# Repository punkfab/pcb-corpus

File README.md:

# pcb-corpus

235 real KiCad boards from 170 open-source hardware repositories, prepared as a benchmark for
PCB placement and routing tools. Each board comes as its designer shipped it and as an unrouted copy, with
its own project rules.

It exists because the public routing benchmarks are built on KiCad 5 files with no project file, so every
board is judged against KiCad's default rules. These are current designs judged against their own.

## What is in a board folder

| file | what it is |
|---|---|
| `board.kicad_pcb` | the designer's board, unmodified |
| `board.kicad_pro` | its project file: net classes, clearances, DRC severities |
| `board.kicad_dru` | its custom rules, when the project has them |
| `unrouted.kicad_pcb` | the same board with tracks, vias and zone fills removed; placement kept |
| `LICENSE` (or as named upstream) | the source repository's licence file at the pinned commit |
| `SOURCE.json` | repository, commit, path, licence, and what was changed |

`manifest.json` lists every board with its statistics. `splits.json` is the original three-way split by size:
easy (under 40 connections, 37 boards), medium (40 to 149, 112) and hard (150 and up, 86).

## What qualified

A board is here if:

- its repository carries an open-hardware or permissive licence that GitHub recognises,
- a `.kicad_pro` sits beside the `.kicad_pcb`,
- it opens in KiCad 9, has 1 to 4 copper layers and at least 5 parts on nets,
- and its designer's routing leaves no connection open.

158 of the 235 boards have error-level DRC violations under their own rules as designed. `ref_drv` in
the manifest is that count. For a "clean pass" comparison (fully connected, zero DRC errors), use the
77 boards where it is 0.

Mix: 178 two-layer, 57 four-layer.
Licences: MIT 75, GPL-3.0 67, CERN-OHL-S-2.0 25, CERN-OHL-P-2.0 25, Apache-2.0 19, CC-BY-SA-4.0 10, CERN-OHL-W-2.0 5, CC-BY-4.0 4, BSD-3-Clause 3, CC0-1.0 2.

## Groups and difficulty

`features.json` describes every board: size and density, stackup, packages, project rules, how its designer
routed it, wiring estimates, and what is on it. `groups.json` sorts the boards into overlapping groups, and
[GROUPS.md](GROUPS.md) has the full table with a baseline score for each group.

| kind | groups |
|---|---|
| size | `small` 37, `medium` 112, `large` 66, `xlarge` 20 |
| stackup | `two-layer` 178, `four-layer` 57, `inner-planes` 57, `no-pour` 13 |
| technology | `through-hole` 43, `surface-mount` 72, `double-sided` 99, `fine-pitch` 113, `bga` 7, `dense` 60, `sparse` 59 |
| constraints | `diff-pairs` 80, `shaped-outline` 85, `cutouts` 55, `keepouts` 63, `net-classes` 114, `custom-rules` 22, `tight-rules` 56 |
| wiring | `tangled` 59, `untangled` 55, `via-heavy` 63, `single-sided-routing` 23 |
| on the board | `usb`, `usb-c`, `ethernet`, `can-rs485`, `wireless`, `crystal`, `switching-regulator`, `battery`, `display`, `audio`, `motor-power`, `memory`, `sensor`, `fpga`, `keyboard`, `addressable-leds` |
| controller | `esp32`, `rp2040`, `stm32`, `avr`, `nrf`, `teensy-module` |
| reference | `clean-reference` 77: zero DRC errors as designed |

The "on the board" and controller groups are detected from net, footprint and value names. They are
useful for slicing results, not ground truth; expect some mislabels.

**Difficulty is measured.** Each board's designer placement is routed by a baseline router and judged by
KiCad DRC. The first baseline is [TraceMaker](https://github.com/DingoOz/TraceMaker) with a 30-second budget
(`baselines/tracemaker-30s.json`):

| tier | meaning | boards | median connections |
|---|---|---|---|
| `difficulty-solved` | routed clean: fully connected, zero error-level DRC | 48 | 58 |
| `difficulty-connects` | 98% or more connected, but not clean | 101 | 88 |
| `difficulty-open` | under 98% connected | 86 | 207 |

Over all 235 boards that baseline routes 20% clean and connects 94.5% of connections. On the 77
`clean-reference` boards it routes 49% clean. What separates easy from hard, by share routed clean:

- **Easiest:** `untangled` 45%, `single-sided-routing` 43%, `small` 43%, `no-pour` 38%, `through-hole` 35%.
- **Hardest:** `xlarge`, `fpga` and `bga` 0%, `tangled` 3%, `crystal` 6%, `large` 8%, `double-sided` 9%, `fine-pitch` 10%, `four-layer` 11%.

The tiers will move as baselines are added: a board is `solved` once any baseline routes it clean.
Add one with `python3 tools/baseline.py --name <name> --cmd '<router> {in} -o {out}'`, then
`python3 tools/groups.py`.

## Using it

- **Routing:** route `unrouted.kicad_pcb`, refill the zones, and run
  `kicad-cli pcb drc --severity-error` on the result with `board.kicad_pro` copied beside it.
- **Placement:** move the parts of `unrouted.kicad_pcb`, then route and judge the same way. The designer's
  placement is the reference.
- A router that reads the board file directly will treat a stale zone fill as copper in its way. The
  unrouted boards have their fills cleared for that reason; refill after routing, before DRC.

The collector that built this, and harnesses that run it, are in
[punkfab/circuit-skills](https://github.com/punkfab/circuit-skills) under `evals/corpus`.

## Licences

This repository is a collection. **Each board keeps the licence of its source repository**, copied into
its folder; see [ATTRIBUTION.md](ATTRIBUTION.md) for the full list. Several are share-alike (GPL-3.0,
CERN-OHL-S, CC-BY-SA): if you redistribute or modify those boards, their terms apply to you.
`unrouted.kicad_pcb` is a modified copy (routing removed) under the same licence as its board.

The licence recorded for a board is the one GitHub detects for its repository. If you are an author
and a board here is under different terms than recorded, or you want it removed, open an issue and it
will be taken down.

The manifest, splits, README and attribution files are released under CC0-1.0.

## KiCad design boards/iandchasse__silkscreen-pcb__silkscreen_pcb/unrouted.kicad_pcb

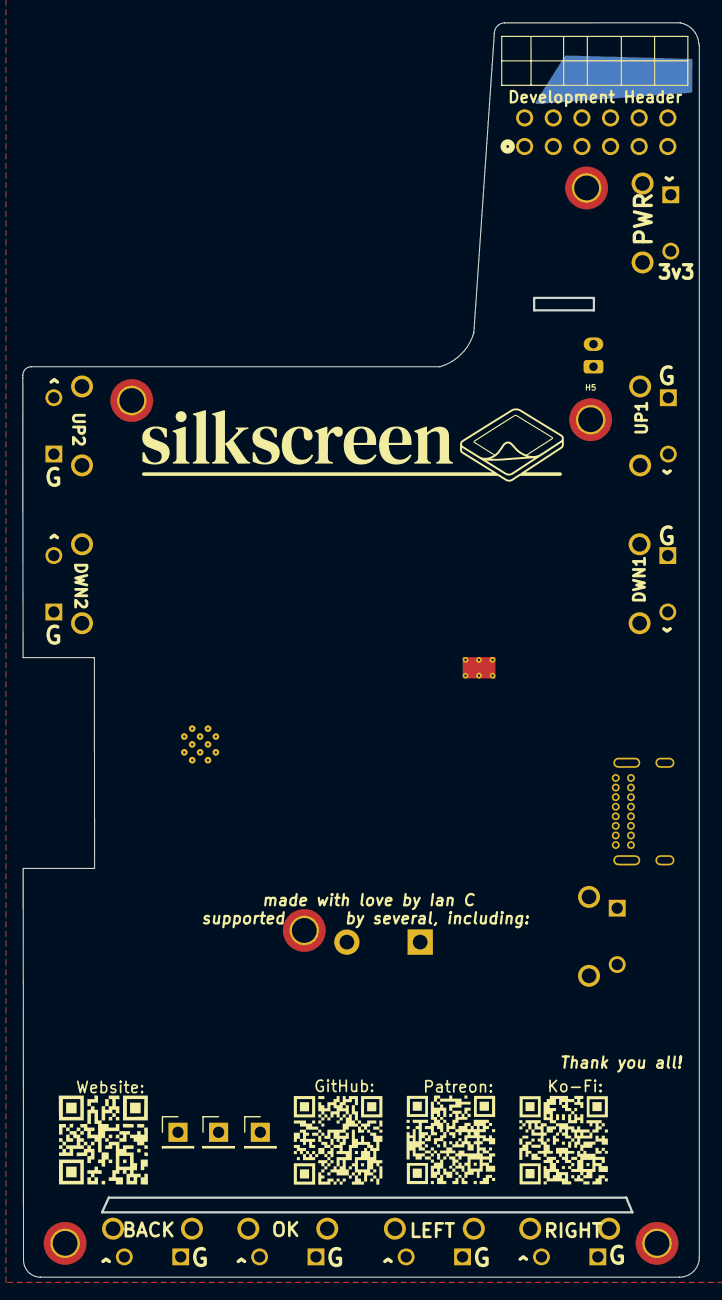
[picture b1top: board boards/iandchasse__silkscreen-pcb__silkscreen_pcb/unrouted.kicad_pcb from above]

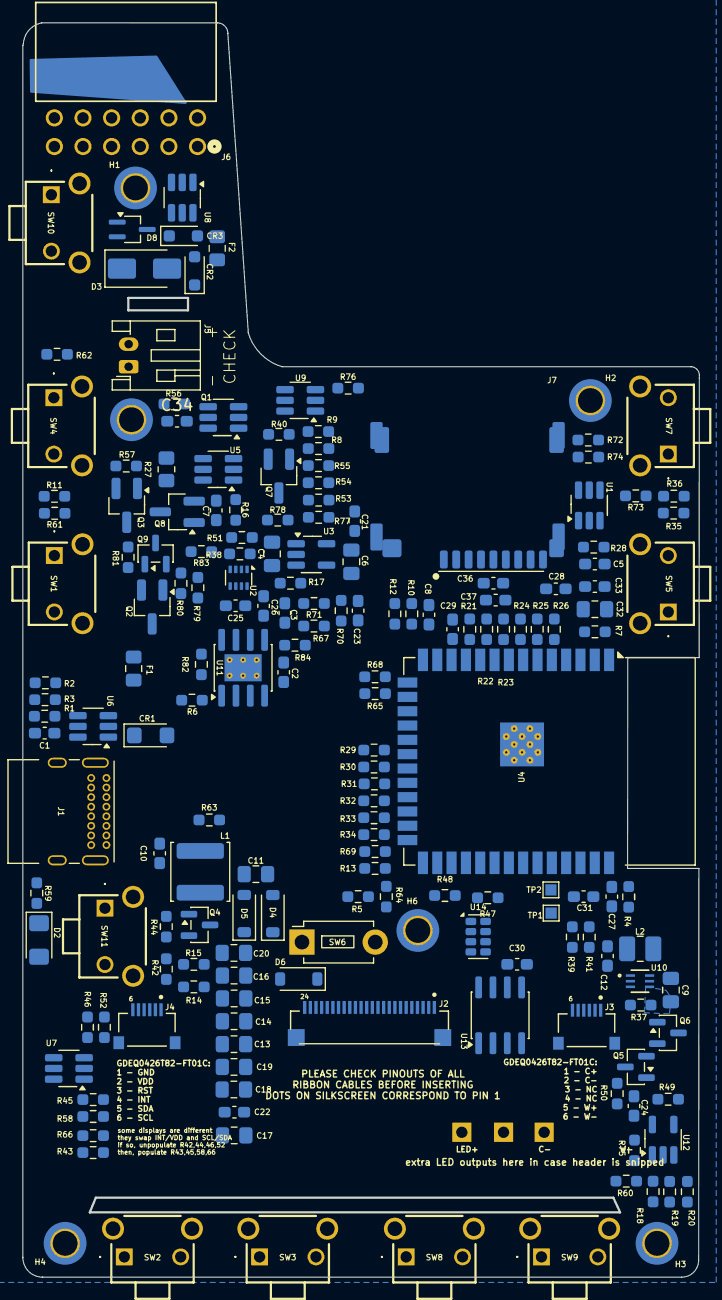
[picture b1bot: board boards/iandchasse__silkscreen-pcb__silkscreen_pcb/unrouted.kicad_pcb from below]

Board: 2 copper layers, 60.0 x 111.3 mm, 185 parts (181 on the bottom side), 114 nets, no tracks yet.

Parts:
C1: 1n; C_0603_1608Metric_Pad1.08x0.95mm_HandSolder
C2: 10u/25V; C_0603_1608Metric_Pad1.08x0.95mm_HandSolder
C3: 10u; C_0603_1608Metric_Pad1.08x0.95mm_HandSolder
C4, C6, C32: 22u; C_0805_2012Metric_Pad1.18x1.45mm_HandSolder
C5, C8, C21, C22, C25, C26, C37: 1u; C_0603_1608Metric_Pad1.08x0.95mm_HandSolder
C7, C23, C24, C30, C31, C33, C36: 0.1u; C_0603_1608Metric_Pad1.08x0.95mm_HandSolder
C9, C11, C13, C14, C15, C16, C17: 4.7u/50V; C_0805_2012Metric_Pad1.18x1.45mm_HandSolder
C10, C12: 4.7u; C_0603_1608Metric_Pad1.08x0.95mm_HandSolder
C18, C19, C20: 1u/50V; C_0805_2012Metric_Pad1.18x1.45mm_HandSolder
C27, C28, C29, C34: 2.2n; C_0603_1608Metric_Pad1.08x0.95mm_HandSolder
CR1: SMF6.5CA; D_SMF
CR2, CR3: TSD05CDYFR; D_SOD-323_HandSoldering
D2: LED; LED_1206_3216Metric_Pad1.42x1.75mm_HandSolder
D3: SMAJ26A; D_SMA
D4, D5, D6: B5819W; D_SOD-123
D8: PESD2IVN-UX; SOT-323_SC-70_Handsoldering
F1: 0805L100WR; Fuse_0805_2012Metric_Pad1.15x1.40mm_HandSolder
F2: 0805L075WR; Fuse_0805_2012Metric_Pad1.15x1.40mm_HandSolder
H1, H2, H3, H4, H5, H6: MountingHole_Pad; MountingHole_2.2mm_M2_DIN965_Pad_TopBottom
J1: USB_C_Receptacle; USB_C_Receptacle_GCT_USB4085
J2: FH34SRJ-24S-0.5SH_50_; HRS_FH34SRJ-24S-0.5SH_50_
J3, J4: FH34SRJ-6S-0.5SH_50_; HRS_FH34SRJ-6S-0.5SH_50_
J5: Conn_01x02; JST_PH_S2B-PH-K_1x02_P2.00mm_Horizontal
J6: PPPC062LJBN-RC; CONN_PPPC062LJBN-RC_SUL
J7: Micro_SD_Card; microSD_PushPush_TFPUSH-MEM2075
L1: 47uH; L_APV_ANR5040
L2: 10u; L_1008_2520Metric_Pad1.43x2.20mm_HandSolder
Q1: FS8205A; SOT-23-6_Handsoldering
Q2, Q3, Q7, Q8: AO3401A; SOT-23_Handsoldering
Q4: IRLML6346TRPBF; SOT-23
Q5, Q6, Q9: BSS138; SOT-23
R1, R10, R12, R15, R39, R49, R50, R70, R80, R81, R82: 1M; R_0603_1608Metric_Pad0.98x0.95mm_HandSolder
R2, R3: 5.1k; R_0603_1608Metric_Pad0.98x0.95mm_HandSolder
R4, R5, R7, R8, R9, R13, R28, R53, R54, R55, R56, R62, R72: 10k; R_0603_1608Metric_Pad0.98x0.95mm_HandSolder
R6: 4.7k; R_0603_1608Metric_Pad0.98x0.95mm_HandSolder
R11: 12k; R_0603_1608Metric_Pad0.98x0.95mm_HandSolder
R14: 2.2; R_0603_1608Metric_Pad0.98x0.95mm_HandSolder
R16, R78: 1k; R_0603_1608Metric_Pad0.98x0.95mm_HandSolder
R17: 2M; R_0603_1608Metric_Pad0.98x0.95mm_HandSolder
R18: 5.6k; R_0603_1608Metric_Pad0.98x0.95mm_HandSolder
R19: 20k; R_0603_1608Metric_Pad0.98x0.95mm_HandSolder
R20: 56k; R_0603_1608Metric_Pad0.98x0.95mm_HandSolder
R21, R22, R23, R24, R25, R26, R29, R30, R31, R32, R33, R34, R65, R68, R69: 33; R_0603_1608Metric_Pad0.98x0.95mm_HandSolder
R27: 0; R_0805_2012Metric_Pad1.20x1.40mm_HandSolder
R35: 33k; R_0603_1608Metric_Pad0.98x0.95mm_HandSolder
R36: 68k; R_0603_1608Metric_Pad0.98x0.95mm_HandSolder
R37: 15; R_0603_1608Metric_Pad0.98x0.95mm_HandSolder
R38: 300k; R_0603_1608Metric_Pad0.98x0.95mm_HandSolder
R40, R51, R75, R76, R77, R79: 100k; R_0603_1608Metric_Pad0.98x0.95mm_HandSolder
R41: 120k; R_0603_1608Metric_Pad0.98x0.95mm_HandSolder
R42, R43, R44, R45, R46, R52, R58, R66, R73, R74: 0; R_0603_1608Metric_Pad0.98x0.95mm_HandSolder
R47, R48: 2.2k; R_0603_1608Metric_Pad0.98x0.95mm_HandSolder
R57: 10M; R_0603_1608Metric_Pad0.98x0.95mm_HandSolder
R59: 2k; R_0603_1608Metric_Pad0.98x0.95mm_HandSolder
R60, R61, R63, R64, R83: 100; R_0603_1608Metric_Pad0.98x0.95mm_HandSolder
R67: 510k; R_0603_1608Metric_Pad0.98x0.95mm_HandSolder
R71: 200k; R_0603_1608Metric_Pad0.98x0.95mm_HandSolder
R84: 1; R_0603_1608Metric_Pad0.98x0.95mm_HandSolder
SW1, SW2, SW3, SW4, SW5, SW7, SW8, SW9, SW10, SW11: SW_Push; MJTP1117
SW6: SW_Push; SW_PUSH_1P1T_6x3.5mm_H4.3_APEM_MJTP1243
TP1, TP2: TestPoint; TestPoint_Pad_1.0x1.0mm
TP3, TP4, TP5: TestPoint; PinHeader_1x01_P2.54mm_Vertical
U1, U6, U7, U8, U9: TPD4E1U06DBVR; SOT-23-6_Handsoldering
U2: TPS2116DRL; SOT-583-8
U3: TLV75533PDBV; SOT-23-5_HandSoldering
U4: ESP32-S3-WROOM-1
U5: DW01A; SOT-23-6_Handsoldering
U10: TPS923610DRLR; U_DRL0006A_6L_TEX-M
U11: TP4056-42-ESOP8; SOIC-8-1EP_3.9x4.9mm_P1.27mm_EP2.41x3.3mm_ThermalVias
U12: 74LVC1G04; SOT-23-5_HandSoldering
U13: DS3231MZ; SOIC-8_3.9x4.9mm_P1.27mm
U14: RV-8263-C7; MicroCrystal_C7_SON-8_1.5x3.2mm_P0.9mm

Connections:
3V3: C6.1, C10.2, C21.1, C22.2, C24.1, C30.1, C32.1, C33.1, CR2.1 (I/O), J2.15, J2.16, J6.7, L1.2, Q2.2 (S), Q7.2 (S), R4.2, R5.2, R7.1, R13.1, R28.2, R40.2, R42.1, R47.1, R48.1, R66.1, R70.2, R74.1, R81.2, SW10.2, U3.5 (OUT), U4.2 (3V3), U12.5 (VCC), U13.6 (VBAT), U14.5 (VDD)
/COLOR_SEL_INV: Q6.1 (G), U12.4
/DET_NODE: Q2.1 (G), Q9.3 (D), R81.1
/GDR: J2.2, Q4.1 (G), R15.2
/P+_FUSE: CR3.1 (I/O), F2.1, J6.12
/PIN_2: J4.2, R42.2, R43.2
/PIN_4: J4.4, R44.2, R66.2, U7.1
/PIN_5: J4.5, R45.2, R46.2, U7.4
/PIN_6: J4.6, R52.2, R58.2, U7.6
/PR1: R38.2, R51.1, U2.4 (PR1)
/RESE: J2.3, Q4.2 (S), R14.2
B+: J5.2, Q3.2 (S), R57.2, R79.1
B-: C7.2, C34.2, J5.1, Q1.1, Q9.2 (S), R56.2, R80.1, U5.6 (GND)
BAT_MONIT: C8.1, R10.1, R12.2, U4.12 (IO8)
BUTTON_ADC_1: C27.2, R4.1, R18.2, R19.2, R20.2, R60.2, U4.39 (IO1)
BUTTON_ADC_2: C28.2, R11.2, R28.1, R35.2, R36.2, R61.2, U4.4 (IO4)
C-: D8.1 (A1), J3.2, J6.11, Q6.3 (D), R49.1, TP4.1
CC1: J1.A5 (CC1), R3.1, U6.4
CC2: J1.B5 (CC2), R2.1, U6.3
CE: Q2.3 (D), R82.2, U11.8 (CE)
CHRG: R67.1, U11.7 (~CHRG)
COLOR_SEL: Q5.1 (G), R75.1, U4.33 (IO40), U12.2
DN: J1.A7 (D-), J1.B7 (D-), U4.13 (USB_D-), U6.1
DP: J1.A6 (D+), J1.B6 (D+), U4.14 (USB_D+), U6.6
EINK_SW: C11.2, D5.2 (A), L1.1, Q4.3 (D)
EPD_BUSY: J2.9, R34.1
EPD_CS: J2.12, R31.1
EPD_DC: J2.11, R32.1
EPD_RST: J2.10, R5.1, R33.1
ESP32_EN: C5.1, R7.2, R63.2, U4.3 (EN)
ESP32_IO0: R13.2, R64.2, U4.27 (IO0)
GND: C1.1, C3.2, C4.2, C5.2, C6.2, C8.2, C9.1, C10.1, C12.1, C13.1, C14.1, C15.1, C16.1, C17.1, C18.1, C19.1, C20.1, C21.2, C22.1, C23.2, C24.2, C25.1, C26.2, C27.1, C28.1, C29.2, C30.2, C31.2, C32.2, C33.2, C36.1, C37.1, CR1.2 (GND), CR2.2 (GND), CR3.2 (GND), D3.2 (A2), D6.1 (K), D8.3 (common), H1.1, H2.1, H3.1, H4.1, H5.1, H6.1, J1.A1 (GND), J1.A12 (GND), J1.B1 (GND), J1.B12 (GND), J2.8, J2.17, J2.S1 (SHIELD), J2.S2 (SHIELD__1), J3.S1 (SHIELD), J3.S2 (SHIELD), J4.1, J4.S1 (SHIELD), J4.S2 (SHIELD), J6.1, J6.4, J7.6 (VSS), J7.9 (SHIELD), Q1.3, Q8.1 (G), R1.1, R2.2, R3.2, R6.2, R10.2, R14.1, R15.1, R16.1, R37.2, R41.2, R49.2, R50.2, R51.2, R59.2, R73.1, R75.2, R76.2, R77.2, R82.1, R84.2, SW1.1, SW2.1, SW3.1, SW4.1, SW5.1, SW6.1, SW8.1, SW9.1, SW11.1, U1.2, U2.1 (GND), U3.2 (GND), U4.1 (GND), U4.40 (GND), U4.41 (GND), U6.2, U7.2, U8.2, U9.2, U10.4 (GND), U11.1 (TEMP), U11.3 (GND), U11.9 (EPAD), U12.3 (GND), U13.2 (VCC), U13.5 (GND), U14.2 (VSS), U14.3 (CLKOE)
I2C_SCL: J6.10, R45.1, R47.2, R52.1, U4.32 (IO39), U8.3, U13.8 (SCL), U14.7 (SCL)
I2C_SDA: J6.8, R46.1, R48.2, R58.1, U4.31 (IO38), U8.4, U13.7 (SDA), U14.8 (SDA)
LDO_IN: C4.1, C12.2, L2.1, U2.2 (VOUT), U2.7 (VOUT), U3.1 (IN), U3.3 (EN), U10.1 (VIN)
LED_MONIT: C31.1, R39.2, R41.1, U4.38 (IO2)
LED_SW: C9.2, D3.1 (A1), J3.1, J3.5, J6.5, R39.1, TP3.1, U10.5 (VOUT)
unnamed: C2.2, R84.1
unnamed: C13.2, J2.20
unnamed: C15.2, J2.22
unnamed: C17.2, J2.5
unnamed: C18.2, J2.18
unnamed: C19.2, J2.19
unnamed: C20.2, J2.24
unnamed: D2.1 (K), R59.1
unnamed: C11.1, D4.1 (K), D6.2 (A)
unnamed: C1.2, J1.S1 (SHIELD), R1.2
unnamed: Q3.3 (D), R27.2
unnamed: Q3.1 (G), R56.1, R57.1
unnamed: Q5.2 (S), Q6.2 (S), R37.1, U10.3 (FB)
unnamed: Q7.1 (G), R40.1, R78.2
unnamed: Q8.3 (D), R27.1
unnamed: Q9.1 (G), R79.2, R80.2
unnamed: R11.1, SW4.2
unnamed: R18.1, SW3.2
unnamed: R19.1, SW8.2
unnamed: R20.1, SW9.2
unnamed: R35.1, SW5.2
unnamed: R36.1, R72.2, SW7.2
unnamed: R60.1, SW2.2
unnamed: R61.1, SW1.2
unnamed: R62.1, SW10.1
unnamed: R63.1, SW11.2
unnamed: R64.1, SW6.2
unnamed: R73.2, R74.2, SW7.1
unnamed: R68.2, U4.15 (IO3)
unnamed: R26.1, U4.5 (IO5)
unnamed: R25.1, U4.6 (IO6)
unnamed: R24.1, U4.7 (IO7)
unnamed: R29.2, U4.20 (IO12)
unnamed: R30.2, U4.21 (IO13)
unnamed: R31.2, U4.22 (IO14)
unnamed: R23.1, U4.8 (IO15)
unnamed: R22.1, U4.9 (IO16)
unnamed: R21.1, U4.10 (IO17)
unnamed: R32.2, U4.23 (IO21)
unnamed: R69.1, U4.26 (IO45)
unnamed: R65.1, U4.16 (IO46)
unnamed: R33.2, U4.24 (IO47)
unnamed: R34.2, U4.25 (IO48)
unnamed: C34.1, R16.2, U5.2 (CS)
unnamed: Q1.4, U5.3 (OC)
unnamed: Q1.6, U5.1 (OD)
unnamed: C7.1, R83.1, U5.5 (VCC)
unnamed: R6.1, U11.2 (PROG)
P+: C3.1, C26.1, F2.2, Q8.2 (S), R12.1, R83.2, U2.6 (VIN2), U11.5 (BAT)
PREVGH: C14.2, D5.1 (K), J2.21
PREVGL: C16.2, D4.2 (A), J2.23
PWM_LED: U4.35 (IO42), U10.2 (ADIM)
PWR_BUTTON: C29.1, R62.2, R72.1, R76.1, U4.11 (IO18)
RX: TP1.1, U4.36 (RXD0)
SD_ACTIVATE: R78.1, U4.18 (IO10)
SD_CLK: J7.5 (CLK), R24.2, U1.4
SD_CMD: J7.3 (CMD), R23.2, R55.1, U1.6
SD_DAT0: J7.7 (DAT0), R8.1, R25.2, U9.3
SD_DAT1: J7.8 (DAT1), R9.1, R26.2, U9.1
SD_DAT2: J7.1 (DAT2), R21.2, R53.1, U1.3
SD_DAT3: J7.2 (DAT3/CD), R22.2, R54.1, U1.1
SD_VDD: C36.2, C37.2, J7.4 (VDD), Q7.3 (D), R8.2, R9.2, R53.2, R54.2, R55.2, R77.1
SPI_MOSI: J2.14, R29.1
SPI_SCK: J2.13, R30.1
ST: R17.1, U2.8 (ST)
STDBY: R71.1, U11.6 (~STDBY)
TPS_SW_NODE: L2.2, U10.6 (SW)
TP_INT: R43.1, R44.1, U4.34 (IO41)
TP_RST: J4.3, U4.19 (IO11), U7.3
TX: TP2.1, U4.37 (TXD0)
UNUSED_GPIO_3: J6.9, R68.1, U8.6
UNUSED_GPIO_45: J6.3, R69.2, U8.1
UNUSED_GPIO_46: J6.2, R65.2, U9.6
USB_STAT: C23.1, R17.2, R67.2, R70.1, R71.2, U4.17 (IO9)
USB_VBUS: C2.1, C25.2, D2.2 (A), F1.2, R38.1, U2.3 (VIN1), U2.5 (MODE), U11.4 (V_{CC})
VBUS_PRE_FUSE: CR1.1 (I/O), F1.1, J1.A4 (VBUS), J1.A9 (VBUS), J1.B4 (VBUS), J1.B9 (VBUS)
W-: D8.2 (A2), J3.6, J6.6, Q5.3 (D), R50.1, TP5.1

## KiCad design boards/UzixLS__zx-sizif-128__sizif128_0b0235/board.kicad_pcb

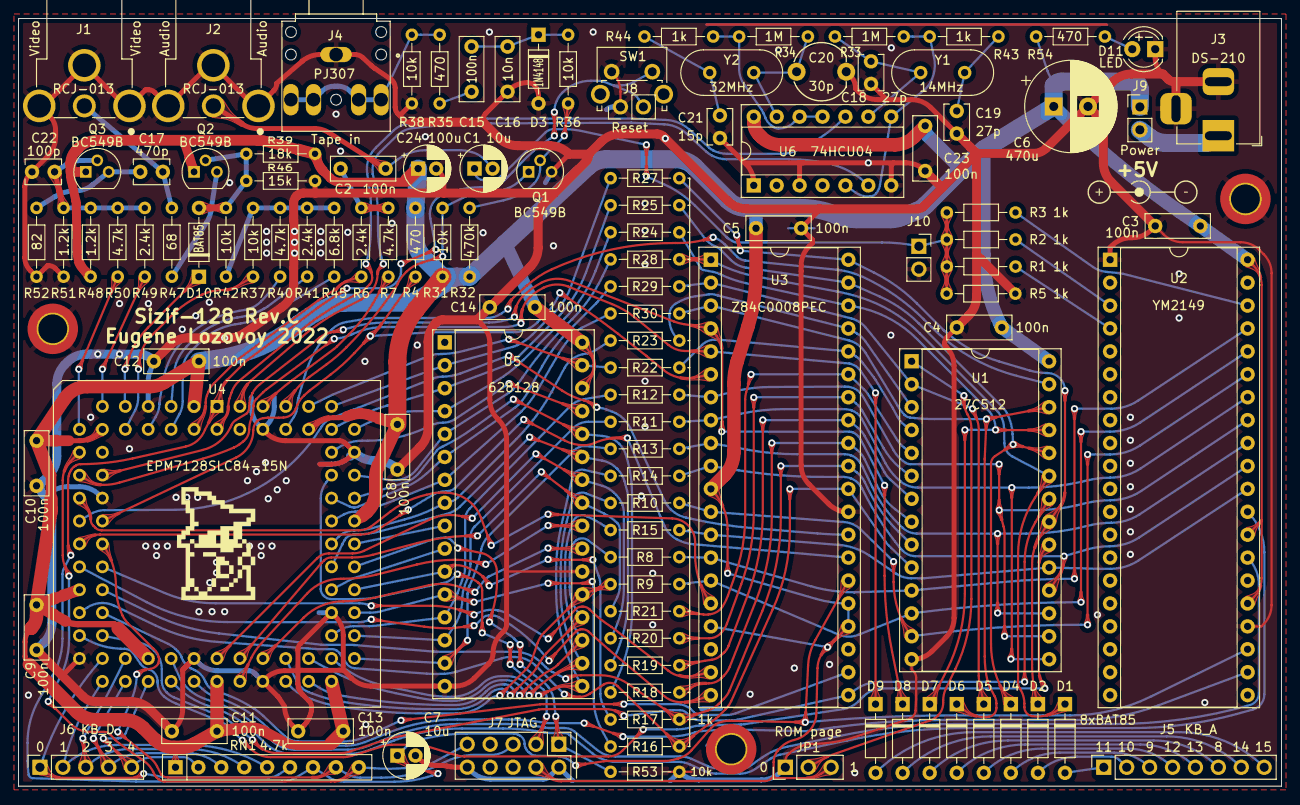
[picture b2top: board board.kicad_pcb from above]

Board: 2 copper layers, 140.0 x 85.1 mm, 117 parts (0 on the bottom side), 121 nets.

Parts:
C1, C7: 10u; CP_Radial_D5.0mm_P2.00mm
C2, C3, C4, C5, C8, C9, C10, C11, C12, C13, C14, C15, C23: 100n; C_Disc_D7.0mm_W2.5mm_P5.00mm
C6: 470u; CP_Radial_D10.0mm_P3.80mm
C16: 10n; C_Disc_D7.0mm_W2.5mm_P5.00mm
C17: 470p; C_Disc_D3.8mm_W2.6mm_P2.50mm
C18, C19: 27p; C_Disc_D3.8mm_W2.6mm_P2.50mm
C20: 30p; C_Trim_D6.3mm_P5.50mm
C21: 15p; C_Disc_D3.8mm_W2.6mm_P2.50mm
C22: 100p; C_Disc_D3.8mm_W2.6mm_P2.50mm
C24: 100u; CP_Radial_D5.0mm_P2.00mm
D1, D2, D4, D5, D6, D7, D8, D9, D10: BAT85; D_DO-35_SOD27_P7.62mm_Horizontal
D3: 1N4148; D_DO-35_SOD27_P7.62mm_Horizontal
D11: LED; LED_D4.0mm
H1, H2, H3: MountingHole; MountingHole_3.2mm_M3_DIN965_Pad_TopOnly
J1, J2: RCJ-013; CUI_RCJ-013
J3: DS-210; BarrelJack_Horizontal
J4: PJ307; SWITCHCRAFT_35RAPC4BHN2
J5: Conn_01x08; PinSocket_1x08_P2.54mm_Vertical
J6: Conn_01x05; PinSocket_1x05_P2.54mm_Vertical
J7: Conn_02x05; PinHeader_2x05_P2.54mm_Vertical
J8, J9: Conn_01x02; PinHeader_1x02_P2.54mm_Vertical
J10: Conn_01x02_Female; PinSocket_1x02_P2.54mm_Vertical
JP1: Jumper_3_Bridged12; PinHeader_1x03_P2.54mm_Vertical
LOGO1: logo; black-mage-12.5x8.6-r
LOGO2: logo; dc_center_positive_big
Q1, Q2, Q3: BC549B; TO-92
R1, R2, R3, R5, R8, R9, R10, R11, R12, R13, R14, R15, R16, R17, R18, R19, R20, R21, R22, R23, R24, R25, R27, R28, R29, R30, R43, R44: 1k; R_Axial_DIN0204_L3.6mm_D1.6mm_P7.62mm_Horizontal
R4, R35, R54: 470; R_Axial_DIN0204_L3.6mm_D1.6mm_P7.62mm_Horizontal
R6, R41, R49: 2.4k; R_Axial_DIN0204_L3.6mm_D1.6mm_P7.62mm_Horizontal
R7, R40, R50: 4.7k; R_Axial_DIN0204_L3.6mm_D1.6mm_P7.62mm_Horizontal
R31, R36, R37, R38, R42, R53: 10k; R_Axial_DIN0204_L3.6mm_D1.6mm_P7.62mm_Horizontal
R32: 470k; R_Axial_DIN0204_L3.6mm_D1.6mm_P7.62mm_Horizontal
R33, R34: 1M; R_Axial_DIN0204_L3.6mm_D1.6mm_P7.62mm_Horizontal
R39: 18k; R_Axial_DIN0204_L3.6mm_D1.6mm_P7.62mm_Horizontal
R45: 6.8k; R_Axial_DIN0204_L3.6mm_D1.6mm_P7.62mm_Horizontal
R46: 15k; R_Axial_DIN0204_L3.6mm_D1.6mm_P7.62mm_Horizontal
R47: 68; R_Axial_DIN0204_L3.6mm_D1.6mm_P7.62mm_Horizontal
R48, R51: 1.2k; R_Axial_DIN0204_L3.6mm_D1.6mm_P7.62mm_Horizontal
R52: 82; R_Axial_DIN0204_L3.6mm_D1.6mm_P7.62mm_Horizontal
RN1: 4.7k; R_Array_SIP9
SW1: SW_Push; SW_Tactile_SPST_Angled_PTS645Vx83-2LFS
U1: 27C512; DIP-28_W15.24mm_Socket
U2: YM2149; DIP-40_W15.24mm_Socket
U3: Z84C0008PEC; DIP-40_W15.24mm_Socket
U4: EPM7128SLC84-15N; PLCC-84_THT-Socket
U5: 628128; DIP-32_W15.24mm_Socket
U6: 74HCU04; DIP-14_W7.62mm_Socket
Y1: 14MHz; Crystal_HC49-U_Vertical
Y2: 32MHz; Crystal_HC49-U_Vertical

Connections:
+5V: C3.2, C4.2, C5.2, C6.1, C8.2, C9.2, C10.2, C11.2, C12.2, C13.2, C14.2, C23.2, C24.1, J7.4, J9.1, JP1.3 (B), Q2.1 (C), Q3.1 (C), R4.2, R31.1, R32.1, R39.2, R48.1, R54.1, RN1.1 (common), U1.28 (VCC), U2.25 (A8), U2.28 (BC2), U2.40 (VCC), U3.11 (VCC), U3.17 (~NMI), U3.24 (~WAIT), U3.25 (~BUSRQ), U4.3 (VCCINT), U4.13 (VCCIO), U4.26 (VCCIO), U4.38 (VCCIO), U4.43 (VCCINT), U4.53 (VCCIO), U4.66 (VCCIO), U4.78 (VCCIO), U5.30 (CS2), U5.32 (VCC), U6.14 (VCC)
A0: R16.1, U1.10 (A0), U3.30 (A0), U4.28 (IO)
A1: R17.1, U1.9 (A1), U3.31 (A1), U4.27 (IO)
A2: R18.1, U1.8 (A2), U3.32 (A2)
A3: R19.1, U1.7 (A3), U3.33 (A3)
A4: R20.1, U1.6 (A4), U3.34 (A4)
A5: R21.1, U1.5 (A5), U3.35 (A5)
A6: R22.1, U1.4 (A6), U3.36 (A6)
A7: R23.1, U1.3 (A7), U3.37 (A7)
A8: D7.1 (K), R24.1, U1.25 (A8), U3.38 (A8)
A9: D4.1 (K), R25.1, U1.24 (A9), U3.39 (A9)
A10: D2.1 (K), R27.1, U1.21 (A10), U3.40 (A10)
A11: D1.1 (K), R28.1, U1.23 (A11), U3.1 (A11)
A12: D5.1 (K), R29.1, U1.2 (A12), U3.2 (A12)
A13: D6.1 (K), R30.1, U1.26 (A13), U3.3 (A13)
A14: D8.1 (K), U3.4 (A14), U4.17 (IO)
A15: D9.1 (K), U3.5 (A15), U4.16 (IO)
AY_BC1: U2.29 (BC1), U4.39 (IO)
AY_BDIR: U2.27 (BDIR), U4.40 (IO)
AY_CLK: U2.22 (CLOCK), U4.41 (IO)
BEEPER: R6.1, U4.4 (IO)
Blue: R37.1, U4.10 (IO)
Bright: R45.1, U4.6 (IO)
CHROMA0: R50.1, U4.12 (IO)
CHROMA1: R49.1, U4.11 (IO)
CLK14: U4.83 (INPUT/GCLK1), U6.6
CLK32: U4.2 (INPUT/OE2/GCLK2), U6.10
CLKCPU: R4.1, U3.6 (~CLK), U4.21 (IO)
Csync: D10.1 (K), U4.9 (IO)
D0: R8.1, U1.11 (D0), U2.37 (DA0), U3.14 (D0)
D1: R9.1, U1.12 (D1), U2.36 (DA1), U3.15 (D1)
D2: R10.1, U1.13 (D2), U2.35 (DA2), U3.12 (D2)
D3: R11.1, U1.15 (D3), U2.34 (DA3), U3.8 (D3)
D4: R12.1, U1.16 (D4), U2.33 (DA4), U3.7 (D4)
D5: R13.1, U1.17 (D5), U2.32 (DA5), U3.9 (D5)
D6: R14.1, U1.18 (D6), U2.31 (DA6), U3.10 (D6)
D7: R15.1, U1.19 (D7), U2.30 (DA7), U3.13 (D7)
GND: C3.1, C4.1, C5.1, C6.2, C7.2, C8.1, C9.1, C10.1, C11.1, C12.1, C13.1, C14.1, C16.1, C18.1, C19.1, C20.2, C21.1, C22.2, C23.1, C24.2, D3.2 (A), D11.1 (K), H1.1, H2.1, H3.1, J1.2 (Ext), J2.2 (Ext), J3.2, J3.3, J4.S, J7.2, J7.10, J8.1, J10.2, JP1.1 (A), Q1.3 (E), R5.1, R38.1, R46.2, R51.1, R52.1, R53.1, SW1.1, U1.14 (GND), U2.1 (VSS), U2.24 (~A9), U3.29 (GND), U4.7 (GNDIO), U4.19 (GNDIO), U4.32 (GNDIO), U4.42 (GNDINT), U4.47 (GNDIO), U4.59 (GNDIO), U4.72 (GNDIO), U4.82 (GNDINT), U5.16 (GND), U5.22 (~CS1), U6.1, U6.3, U6.7 (GND)
Green: R41.1, U4.5 (IO)
KD0: J6.1, RN1.6 (R5), U4.34 (IO)
KD1: J6.2, RN1.5 (R4), U4.33 (IO)
KD2: J6.3, RN1.4 (R3), U4.36 (IO)
KD3: J6.4, RN1.3 (R2), U4.35 (IO)
KD4: J6.5, RN1.2 (R1), U4.37 (IO)
unnamed: C1.1, J10.1, R1.2, R2.2, R3.2, R5.2
unnamed: C2.1, R6.2, R7.2
unnamed: C15.1, R35.2
unnamed: C15.2, C16.2, D3.1 (K), R36.1
unnamed: C17.1, Q3.3 (E), R52.2
unnamed: C18.2, R33.1, U6.9, Y1.1
unnamed: C19.2, R43.1, Y1.2
unnamed: C20.1, R34.1, U6.13, Y2.1
unnamed: C21.2, R44.1, Y2.2
unnamed: C22.1, Q3.2 (B), R48.2, R49.2, R50.2, R51.2
unnamed: D1.2 (A), J5.1
unnamed: D2.2 (A), J5.2
unnamed: D4.2 (A), J5.3
unnamed: D5.2 (A), J5.4
unnamed: D6.2 (A), J5.5
unnamed: D7.2 (A), J5.6
unnamed: D8.2 (A), J5.7
unnamed: D9.2 (A), J5.8
unnamed: D10.2 (A), Q2.2 (B), R39.1, R42.2, R46.1
unnamed: D11.2 (A), R54.2
unnamed: J3.1, J9.2
unnamed: JP1.2 (C), U1.1 (A15)
unnamed: Q1.2 (B), R32.2, R36.2
unnamed: Q2.3 (E), R47.2
unnamed: R1.1, U2.4 (A)
unnamed: R2.1, U2.3 (B)
unnamed: R3.1, U2.38 (C)
unnamed: R33.2, R43.2, U6.5, U6.8
unnamed: R34.2, R44.2, U6.11, U6.12
unnamed: R37.2, R40.2, R41.2, R42.1, R45.2
RA14: U1.27 (A14), U4.80 (IO)
Red: R40.1, U4.8 (IO)
SOUND: C1.2, C2.2, J2.1 (In)
TAPE_IN: J4.R, J4.RN, J4.T, J4.TN, R35.1, R38.2
TAPE_IN0: Q1.1 (C), R31.2, U4.79 (IO)
TAPE_OUT: R7.1, U4.81 (IO)
TCK: J7.1, R53.2, U4.62 (IO/TCK)
TDI: J7.9, RN1.9 (R8), U4.14 (IO/TDI)
TDO: J7.3, U4.71 (IO/TDO)
TMS: J7.5, RN1.8 (R7), U4.23 (IO/TMS)
VA0: R16.2, U4.58 (IO), U5.12 (A0)
VA1: R17.2, U4.60 (IO), U5.11 (A1)
VA2: R18.2, U4.68 (IO), U5.28 (A13)
VA3: R19.2, U4.63 (IO), U5.27 (A8)
VA4: R20.2, U4.44 (IO), U5.26 (A9)
VA5: R21.2, U4.46 (IO), U5.25 (A11)
VA6: R22.2, U4.77 (IO), U5.31 (A15)
VA7: R23.2, U4.65 (IO), U5.8 (A4)
VA8: R24.2, U4.74 (IO), U5.4 (A12)
VA9: R25.2, U4.76 (IO), U5.3 (A14)
VA10: R27.2, U4.75 (IO), U5.2 (A16)
VA11: R28.2, U4.70 (IO), U5.5 (A7)
VA12: R29.2, U4.69 (IO), U5.6 (A6)
VA13: R30.2, U4.67 (IO), U5.7 (A5)
VA14: U4.61 (IO), U5.10 (A2)
VA15: U4.64 (IO), U5.9 (A3)
VA16: U4.48 (IO), U5.23 (A10)
VD0: R8.2, U4.50 (IO), U5.20 (Q6)
VD1: R9.2, U4.49 (IO), U5.21 (Q7)
VD2: R10.2, U4.52 (IO), U5.18 (Q4)
VD3: R11.2, U4.56 (IO), U5.14 (Q1)
VD4: R12.2, U4.57 (IO), U5.13 (Q0)
VD5: R13.2, U4.54 (IO), U5.15 (Q2)
VD6: R14.2, U4.55 (IO), U5.17 (Q3)
VD7: R15.2, U4.51 (IO), U5.19 (Q5)
VIDEO: C17.2, J1.1 (In), R47.1
nINT: U3.16 (~INT), U4.18 (IO)
nIORQ: U3.20 (~IORQ), U4.24 (IO)
nM1: U3.27 (~M1), U4.22 (IO)
nMREQ: U3.19 (~MREQ), U4.25 (IO)
nRD: U1.22 (~OE), U3.21 (~RD), U4.31 (IO)
nRFSH: U3.28 (~RFSH), U4.20 (IO)
nROMCS: U1.20 (~CE), U4.30 (IO)
nRST: C7.1, J8.2, RN1.7 (R6), SW1.2, U2.23 (~RESET), U3.26 (~RESET), U4.1 (INPUT/GCLRN)
nVRD: U4.45 (IO), U5.24 (~OE)
nVWR: U4.73 (IO), U5.29 (~WE)
nWR: U3.22 (~WR), U4.29 (IO)

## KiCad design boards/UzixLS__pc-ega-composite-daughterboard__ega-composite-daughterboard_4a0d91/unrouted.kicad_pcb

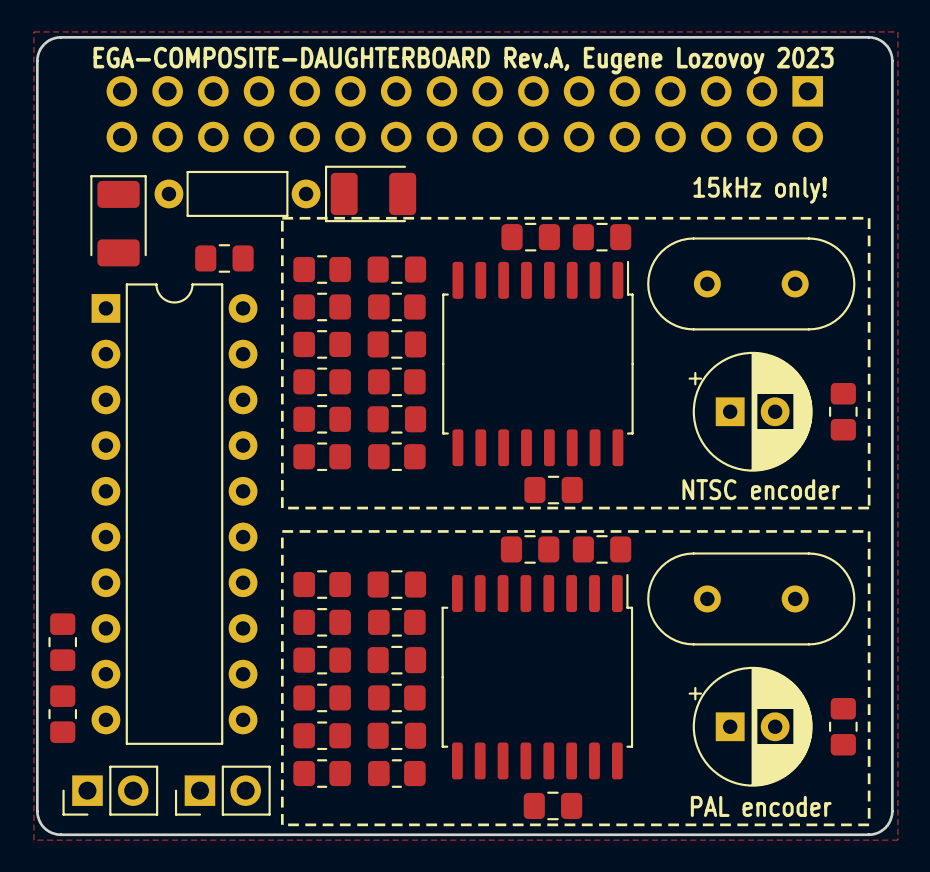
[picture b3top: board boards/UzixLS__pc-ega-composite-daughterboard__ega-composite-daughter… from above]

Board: 2 copper layers, 47.5 x 44.3 mm, 48 parts (1 on the bottom side), 41 nets, no tracks yet.

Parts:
C1, C2, C3, C6, C7, C8: 100n; C_0805_2012Metric_Pad1.18x1.45mm_HandSolder
C4, C9: 220u; CP_Radial_D6.3mm_P2.50mm
C5, C10: 4.3p; C_0805_2012Metric_Pad1.18x1.45mm_HandSolder
C11, C13: 47u/10V; CP_EIA-3528-21_Kemet-B_Pad1.50x2.35mm_HandSolder
C12, C14, C15, C16, C17: 1u; C_0805_2012Metric_Pad1.18x1.45mm_HandSolder
J1: EGA Feature Connector; PinHeader_2x16_P2.54mm_Vertical
JP1, JP2: Jumper_2_Open; PinHeader_1x02_P2.54mm_Vertical
L1: L_FILTER; L_Axial_L5.3mm_D2.2mm_P7.62mm_Horizontal_Vishay_IM-1
R1, R3, R5, R13, R15, R17: 390; R_0805_2012Metric_Pad1.20x1.40mm_HandSolder
R2, R4, R6, R14, R16, R18: 680; R_0805_2012Metric_Pad1.20x1.40mm_HandSolder
R7, R8, R9, R10, R19, R20, R21, R22: 75; R_0805_2012Metric_Pad1.20x1.40mm_HandSolder
R11, R12: 10k; R_0805_2012Metric_Pad1.20x1.40mm_HandSolder
U1, U3: AD724; SOIC-16W_7.5x10.3mm_P1.27mm
U2: ATF16V8; DIP-20_W7.62mm
Y1: 3.579545 MHz; Crystal_HC49-4H_Vertical
Y2: 4.433619 MHz; Crystal_HC49-4H_Vertical

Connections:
+5V: C11.1, C12.2, J1.32, L1.1, R11.1, R12.1, U2.20 (VCC)
+5VA: C13.1, C14.2, C15.2, C16.2, C17.2, L1.2, U1.1 (STDN), U1.4 (AVCC), U1.5 (ENCD), U1.14 (DVCC), U3.4 (AVCC), U3.5 (ENCD), U3.14 (DVCC)
/B0: R6.1, R18.1, U2.19 (IO1)
/B0_IN: J1.23, U2.6 (I6)
/B1: R5.1, R17.1, U2.18 (IO2)
/B1_IN: J1.14, U2.3 (I3)
/G0: R4.1, R16.1, U2.17 (I03)
/G0_IN: J1.22, U2.8 (I8)
/G1: R3.1, R15.1, U2.16 (IO4)
/G1_IN: J1.12, U2.4 (I4)
/HIN: J1.24, U2.7 (I7)
/HSYNC: U1.16 (HSYNC), U2.12 (IO8), U3.16 (HSYNC)
/NTSC: J1.4, R7.1
/PAL: J1.5, R19.1
/R0: R2.1, R14.1, U2.15 (IO5)
/R0_IN: J1.13, U2.2 (I2)
/R1: R1.1, R13.1, U2.14 (IO6)
/R1_IN: J1.15, U2.1 (I1/CLK)
/VIN: J1.25, U2.5 (I5)
/VSYNC: U1.15 (VSYNC), U2.13 (IO7), U3.15 (VSYNC)
GND: C5.2, C10.2, C11.2, C12.1, C13.2, C14.1, C15.1, C16.1, C17.1, J1.1, J1.31, JP1.2 (B), JP2.2 (B), R8.2, R9.2, R10.2, R20.2, R21.2, R22.2, U1.2 (AGND), U1.12 (SELECT), U1.13 (DGND), U2.10 (GND), U3.1 (STDN), U3.2 (AGND), U3.12 (SELECT), U3.13 (DGND), Y1.2, Y2.2
unnamed: C1.2, R1.2, R2.2, R8.1
unnamed: C2.2, R3.2, R4.2, R9.1
unnamed: C3.2, R5.2, R6.2, R10.1
unnamed: C4.2, R7.2
unnamed: C6.2, R13.2, R14.2, R20.1
unnamed: C7.2, R15.2, R16.2, R21.1
unnamed: C8.2, R17.2, R18.2, R22.1
unnamed: C9.2, R19.2
unnamed: JP1.1 (A), R11.2, U2.9 (I9)
unnamed: JP2.1 (A), R12.2, U2.11 (I10/~OE)
unnamed: C3.1, U1.8 (BIN)
unnamed: C4.1, U1.10 (COMP)
unnamed: C5.1, U1.3 (FIN), Y1.1
unnamed: C2.1, U1.7 (GIN)
unnamed: C1.1, U1.6 (RIN)
unnamed: C8.1, U3.8 (BIN)
unnamed: C9.1, U3.10 (COMP)
unnamed: C10.1, U3.3 (FIN), Y2.1
unnamed: C7.1, U3.7 (GIN)
unnamed: C6.1, U3.6 (RIN)

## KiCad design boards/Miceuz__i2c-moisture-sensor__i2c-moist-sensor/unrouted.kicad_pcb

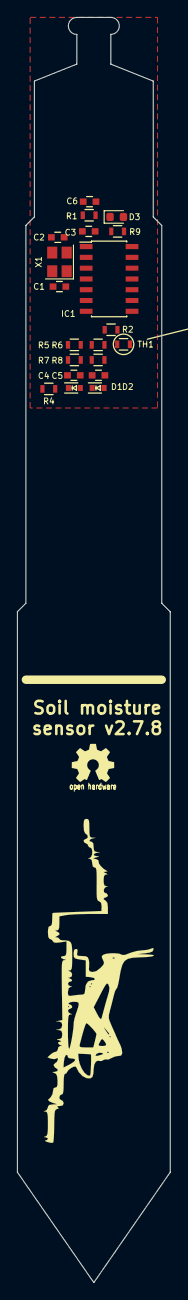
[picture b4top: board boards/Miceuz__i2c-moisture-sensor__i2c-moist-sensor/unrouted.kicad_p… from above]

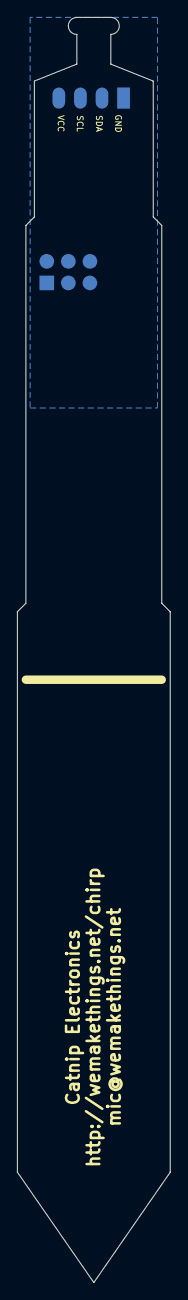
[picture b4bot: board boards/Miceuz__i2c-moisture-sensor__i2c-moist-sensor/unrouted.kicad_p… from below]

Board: 4 copper layers, 18.0 x 149.0 mm, 22 parts (2 on the bottom side), 16 nets, no tracks yet.

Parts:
C1: 33p; C_0603
C2: 33pp; C_0603
C3, C6: 1u; C_0603
C4, C5: 1n; C_0603
D1, D2: BAT54; SOD-523
D3: LED; LED_0603_1608Metric
IC1: ATTINY441-SSU; SOIC-14_3.9x8.7mm_Pitch1.27mm
P1: CONN_02X03; Pin_Header_Straight_2x03
P2: CONN_01X04; Pin_Header_Straight_1x04_Pitch2.54mm
R1: 10k; R_0603
R2: 10k 0.1%; R_0603
R4, R9: 330; R_0603
R5, R6, R7, R8: 1M; R_0603
TH1: NCP18XH103F03RB; R_0603
X1: 16MHz; Crystal_SMD_3225-4pin_3.2x2.5mm

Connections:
/EXCITATION: IC1.5, R4.2
/MISO/SENSE_HIGH: C5.1, D2.2, IC1.8, P1.1, R6.1, R8.2
/MOSI/SDA: IC1.7, P1.4, P2.2
/RESET: C6.1, IC1.4, P1.5, R1.1
/SCK/SCL: IC1.9, P1.3, P2.3
/SENSE_LOW: C4.1, D1.1, IC1.6, R5.1, R7.2
/SENSOR_TRACK: D1.2, D2.1, R4.1
/THERMISTOR: IC1.10, R2.2, TH1.1
GND: C1.2, C2.2, C3.2, C4.2, C5.2, C6.2, IC1.14, P1.6, P2.1, R7.1, R8.1, TH1.2, X1.2, X1.4
unnamed: C1.1, IC1.3, X1.1
unnamed: C2.1, IC1.2, X1.3
unnamed: D3.1, IC1.13
unnamed: D3.2, R9.1
unnamed: IC1.11, R2.1, R5.2, R6.2
unnamed: IC1.12, R9.2
VCC: C3.1, IC1.1, P1.2, P2.4, R1.2

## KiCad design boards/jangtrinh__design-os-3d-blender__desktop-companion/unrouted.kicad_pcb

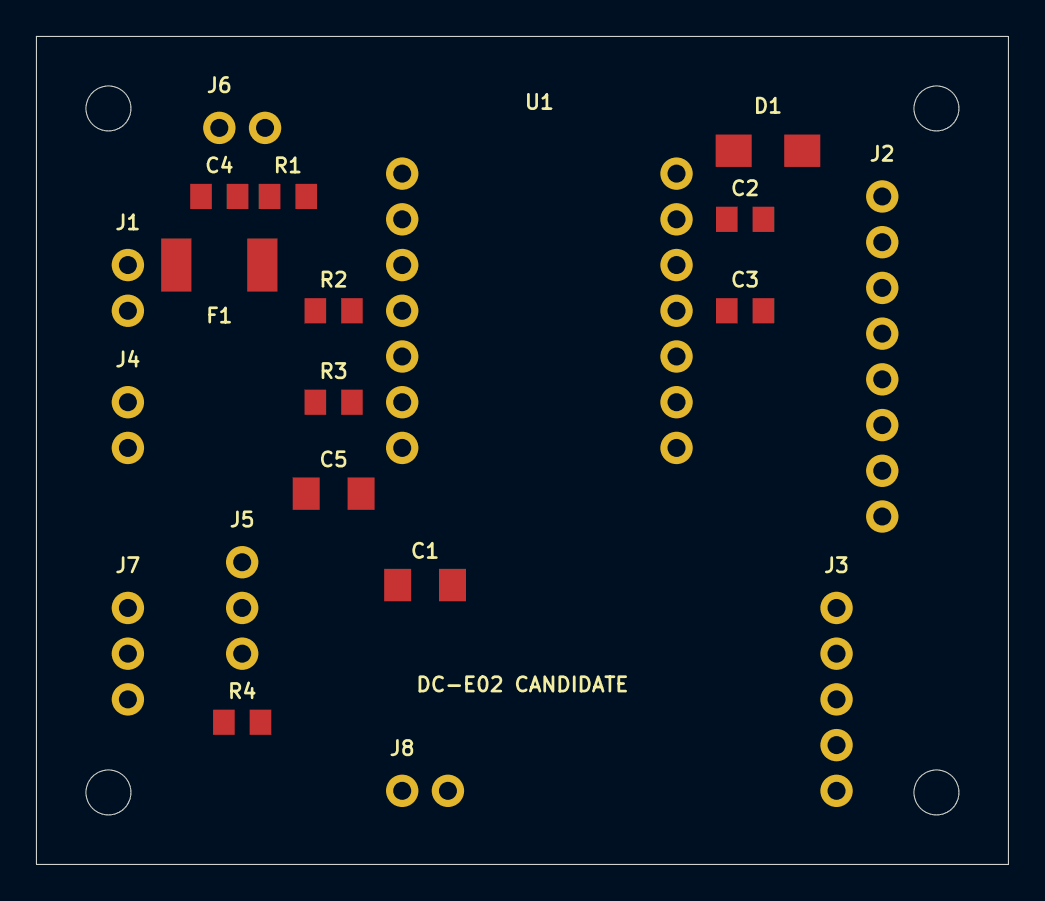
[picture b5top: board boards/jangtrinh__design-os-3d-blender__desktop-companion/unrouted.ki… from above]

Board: 2 copper layers, 54.0 x 46.0 mm, 24 parts (0 on the bottom side), 19 nets, no tracks yet.

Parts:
C1: 47uF_10V_X5R; C1
C2: 100nF_16V_X7R; C2
C3: 10uF_10V_X5R; C3
C4: 100nF_16V_X7R; C4
C5: 47uF_10V_X5R; C5
D1: SS14_SCHOTTKY; D1
F1: MF-MSMF110_16X-2; F1
H1, H2, H3, H4: M2_CLEARANCE
J1: BQ24074_OUT; J1
J2: DISPLAY_5206; J2
J3: I2S_AUDIO_OPTION; J3
J4: POWER_SWITCH; J4
J5: S7V8F5_WIRED; J5
J6: MOMENTARY_BUTTON; J6
J7: CHARGER_PROGRAM_NTC; J7
J8: 103AT2_PACK_SENSOR; J8
R1: 10k_1%; R1
R2: 10k_1%; R2
R3: 10k_1%; R3
R4: 3.57k_1%; R4
U1: Seeed_XIAO_ESP32S3_nonSense; U1

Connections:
+3V3: C3.1, J2.1, R1.2, R2.2, R3.2, U1.12
+5V: C1.1, D1.2, J3.1, J5.3
BUTTON_N: C4.1, J6.1, R1.1, U1.6
COMPUTE_5V: C2.1, D1.1, U1.14
GND: C1.2, C2.2, C3.2, C4.2, C5.2, J1.2, J2.2, J3.2, J5.2, J6.2, J7.2, J8.2, R4.2, U1.13
I2S_BCLK: J3.3, U1.7
I2S_DIN: J3.5, U1.10
I2S_LRCLK: J3.4, U1.8
ISET: J7.1, R4.1
LCD_BL: J2.8, U1.5
LCD_CS: J2.5, R2.1, U1.1
LCD_DC: J2.6, U1.2
LCD_RST: J2.7, R3.1, U1.4
NTC_TS: J7.3, J8.1
SPI_MOSI: J2.4, U1.11
SPI_SCK: J2.3, U1.9
SYS_FUSED: F1.2, J4.1
SYS_RAW: F1.1, J1.1
SYS_SW: C5.1, J4.2, J5.1

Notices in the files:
boards/iandchasse__silkscreen-pcb__silkscreen_pcb/unrouted.kicad_pcb:
Licensed under CERN-OHL-S-2.0
© 2026 idc LLC
